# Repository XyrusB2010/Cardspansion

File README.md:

# Cardspansion
A modular microcontroller system, featuring a customizable MCU

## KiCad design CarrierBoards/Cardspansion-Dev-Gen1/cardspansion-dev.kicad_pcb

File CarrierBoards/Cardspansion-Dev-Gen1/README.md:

# Cardspansion-Dev
This is the first carrier board for the Cardspansion series. It breaks out all of the supported interfaces of the cardspansion-gen1 series (including SDIO, I2S, JTAG, SPI, SWDIO, I2C, and UART). The board also features a CR2032 battery holder for RTC. A DC barrel jack is included, and can handle a voltage up to 12V. Unlike Arduino UNOs, there is a manual switch for selecting the voltage source between USB and DC. The board has 6 LEDs, which indicate power, user LEDs, and UART signals. Most of the components are SMD, except for the DC barrel jack. At the top centre, two push buttons are included for BOOT and RESET, which most MCUs use. PLEASE DO NOT power the board via the 5V pins, as they will damage the onboard voltage regulators. This dev board may be forwards compatible with following generations, although features exclusive to other generations will not be fully compatible. 
## Features
- Supports cardspansion-gen1 cards
- All cardspansion-gen1 interfaces broken out
- Onboard CR2032 battery holder for RTC
- External DC source supported (6-12V)
- Physical slide switch for 5V voltage source (DC Jack, USB)
- LEDs for 3.3V, 5V, 2 User LEDs, UART
- Push buttons for RESET and BOOT
## PCB Render

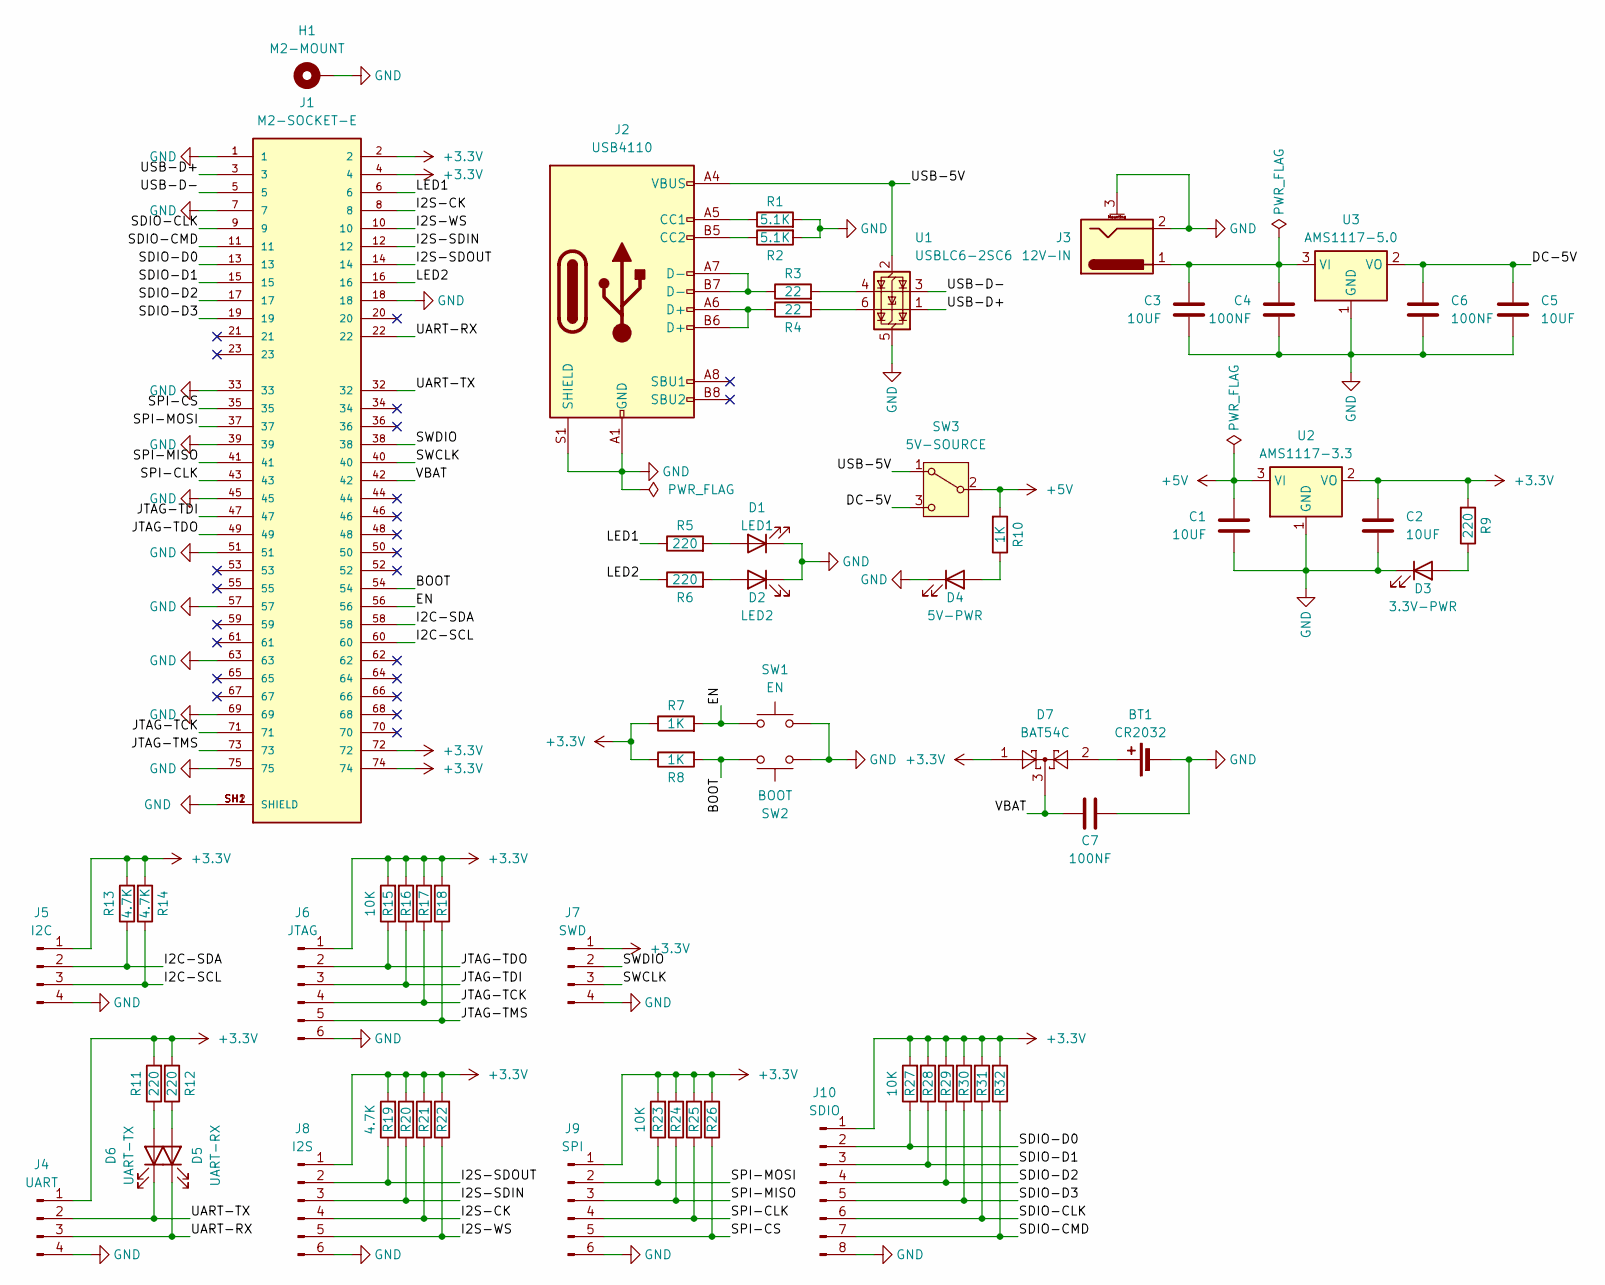
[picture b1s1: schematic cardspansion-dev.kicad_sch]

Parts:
BT1: CR2032; BatteryHolder_Multicomp_BC-2001_1x2032
C1, C2, C3, C5: 10UF; C_0805_2012Metric
C4, C6, C7: 100NF; C_0805_2012Metric
D1: LED1; LED_0805_2012Metric
D2: LED2; LED_0805_2012Metric
D3: 3.3V-PWR; LED_0805_2012Metric
D4: 5V-PWR; LED_0805_2012Metric
D5: UART-RX; LED_0805_2012Metric
D6: UART-TX; LED_0805_2012Metric
D7: BAT54C; SOT-23
H1: M2-MOUNT; MountingHole_2.2mm_M2_Pad
J1: M2-SOCKET-E; TE_2199119-4; PARTREV D
J2: USB4110; USB_C_Receptacle_GCT_USB4110
J3: 12V-IN; BarrelJack_Horizontal
J4: UART; PinHeader_1x04_P2.54mm_Vertical_SMD_Pin1Left
J5: I2C; PinHeader_1x04_P2.54mm_Vertical_SMD_Pin1Left
J6: JTAG; PinHeader_1x06_P2.54mm_Vertical_SMD_Pin1Left
J7: SWD; PinHeader_1x04_P2.54mm_Vertical_SMD_Pin1Left
J8: I2S; PinHeader_1x06_P2.54mm_Vertical_SMD_Pin1Left
J9: SPI; PinHeader_1x06_P2.54mm_Vertical_SMD_Pin1Left
J10: SDIO; PinHeader_1x08_P2.54mm_Vertical_SMD_Pin1Left
R1, R2: 5.1K; R_0805_2012Metric
R3, R4: 22; R_0805_2012Metric
R5, R6, R9, R11, R12: 220; R_0805_2012Metric
R7, R8, R10: 1K; R_0805_2012Metric
R13, R14, R19, R20, R21, R22: 4.7K; R_0805_2012Metric
R15, R16, R17, R18, R23, R24, R25, R26, R27, R28, R29, R30, R31, R32: 10K; R_0805_2012Metric
SW1: EN; SW_Tactile_SPST_NO_Straight_CK_PTS636Sx25SMTRLFS
SW2: BOOT; SW_Tactile_SPST_NO_Straight_CK_PTS636Sx25SMTRLFS
SW3: 5V-SOURCE; SW_SPDT_CK_JS102011SAQN
U1: USBLC6-2SC6; SOT-23-6
U2: AMS1117-3.3; SOT-223-3_TabPin2
U3: AMS1117-5.0; SOT-223-3_TabPin2

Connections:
+3.3V: C2.1, D7.1, J1.2, J1.4, J1.72, J1.74, J4.1, J5.1, J6.1, J7.1, J8.1, J9.1, J10.1, R7.1, R8.1, R9.2, R11.2, R12.2, R13.2, R14.2, R15.2, R16.2, R17.2, R18.2, R19.2, R20.2, R21.2, R22.2, R23.2, R24.2, R25.2, R26.2, R27.2, R28.2, R29.2, R30.2, R31.2, R32.2, U2.2 (VO)
+5V: C1.1, R10.2, SW3.2 (B), U2.3 (VI)
/BOOT: J1.54, R8.2, SW2.1
/DC-5V: C5.1, C6.1, SW3.3 (C), U3.2 (VO)
/EN: J1.56, R7.2, SW1.1
/I2C-SCL: J1.60, J5.3, R14.1
/I2C-SDA: J1.58, J5.2, R13.1
/I2S-CK: J1.8, J8.4, R21.1
/I2S-SDIN: J1.12, J8.3, R20.1
/I2S-SDOUT: J1.14, J8.2, R19.1
/I2S-WS: J1.10, J8.5, R22.1
/JTAG-TCK: J1.71, J6.4, R17.1
/JTAG-TDI: J1.47, J6.3, R16.1
/JTAG-TDO: J1.49, J6.2, R15.1
/JTAG-TMS: J1.73, J6.5, R18.1
/LED1: J1.6, R5.1
/LED2: J1.16, R6.1
/SDIO-CLK: J1.9, J10.6, R31.1
/SDIO-CMD: J1.11, J10.7, R32.1
/SDIO-D0: J1.13, J10.2, R27.1
/SDIO-D1: J1.15, J10.3, R28.1
/SDIO-D2: J1.17, J10.4, R29.1
/SDIO-D3: J1.19, J10.5, R30.1
/SPI-CLK: J1.43, J9.4, R25.1
/SPI-CS: J1.35, J9.5, R26.1
/SPI-MISO: J1.41, J9.3, R24.1
/SPI-MOSI: J1.37, J9.2, R23.1
/SWCLK: J1.40, J7.3
/SWDIO: J1.38, J7.2
/UART-RX: D5.1 (K), J1.22, J4.3
/UART-TX: D6.1 (K), J1.32, J4.2
/USB-5V: J2.A4 (VBUS), J2.A9 (VBUS), J2.B4 (VBUS), J2.B9 (VBUS), SW3.1 (A), U1.2 (GND)
/USB-D+: J1.3, U1.1 (I/O1)
/USB-D-: J1.5, U1.3 (I/O2)
/VBAT: C7.1, D7.3, J1.42
GND: BT1.2 (-), C1.2, C2.2, C3.2, C4.2, C5.2, C6.2, C7.2, D1.1 (K), D2.1 (K), D3.1 (K), D4.1 (K), H1.1 (MP), J1.1, J1.7, J1.18, J1.33, J1.39, J1.45, J1.51, J1.57, J1.63, J1.69, J1.75, J1.SH1 (SHIELD), J1.SH2 (SHIELD), J2.A1 (GND), J2.A12 (GND), J2.B1 (GND), J2.B12 (GND), J2.S1 (SHIELD), J3.2, J3.3 (MountPin), J4.4, J5.4, J6.6, J7.4, J8.6, J9.6, J10.8, R1.2, R2.2, SW1.2, SW2.2, U1.5 (VBUS), U2.1 (GND), U3.1 (GND)
unnamed: BT1.1 (+), D7.2
unnamed: D1.2 (A), R5.2
unnamed: D2.2 (A), R6.2
unnamed: D3.2 (A), R9.1
unnamed: D4.2 (A), R10.1
unnamed: D5.2 (A), R12.1
unnamed: D6.2 (A), R11.1
unnamed: J2.A5 (CC1), R1.1
unnamed: J2.B5 (CC2), R2.1
unnamed: J2.A6 (D+), J2.B6 (D+), R4.1
unnamed: J2.A7 (D-), J2.B7 (D-), R3.1
unnamed: R3.2, U1.4 (I/O2)
unnamed: R4.2, U1.6 (I/O1)
unnamed: C3.1, C4.1, J3.1, U3.3 (VI)

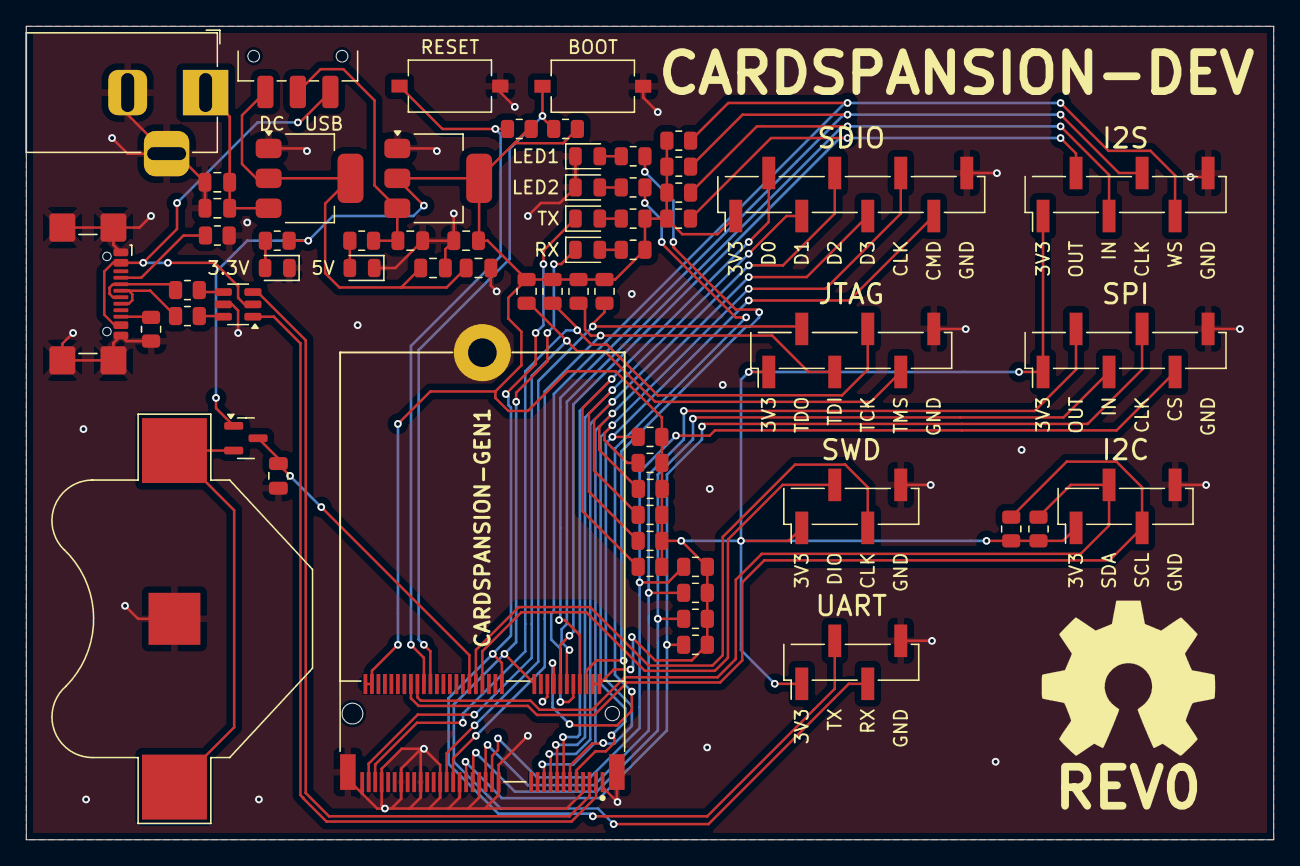
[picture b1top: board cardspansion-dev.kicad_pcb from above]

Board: 2 copper layers, 96.0 x 62.6 mm, 64 parts (0 on the bottom side), 50 nets.

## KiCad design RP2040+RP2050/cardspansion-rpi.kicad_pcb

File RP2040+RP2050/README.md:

# Cardspansion-RPI
The Cardspansion-RPI is the 4th and final MCU to be added to the first generation of the Cardspansion series. It is reccomended to use the Waveshare RP2350-Tiny board, but the RP2040-Tiny is also compatible, at the cost of losing UART, I2C, and LEDs (Will be fixed in a later revision). If you do use the RP2350-Tiny, you also gain access to the SPI, I2S and USB interfaces. The RP2350 and RP2040 have a dedicated USB header on board, but you will need an FPC breakout in order to use it. Just like the Cardspansion-NRF, the Raspberry Pi board is very large, so the silkscreen text on the front layer has to be placed on the side.
## Features
- I2C (RP2350 only)
- UART (RP2350 only)
- SPI
- USB-OTG functionality (Host on dedicated USB pin, OTG configured on PIO)
- 2 LEDs (broken out for carrier board)
## PCB Render

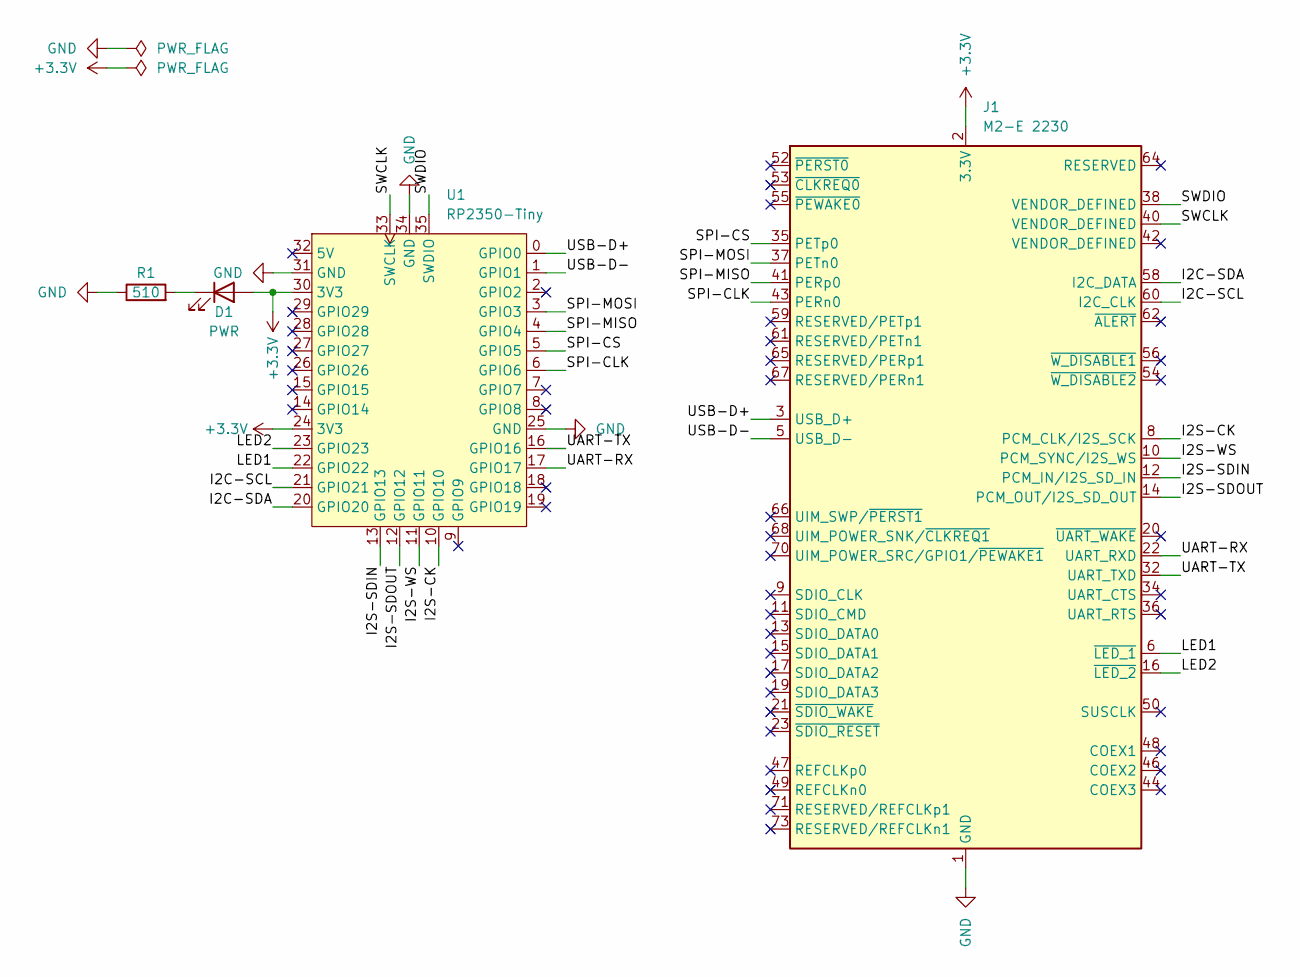
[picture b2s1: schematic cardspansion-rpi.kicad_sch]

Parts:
D1: PWR; LED_0805_2012Metric
J1: M2-E 2230; M2-2230-E
R1: 510; R_0805_2012Metric
U1: RP2350-Tiny

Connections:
+3.3V: D1.2 (A), J1.2 (3.3V), J1.4 (3.3V), J1.72 (3.3V), J1.74 (3.3V), U1.24 (3V3), U1.30 (3V3)
/I2C-SCL: J1.60 (I2C_CLK), U1.21 (GPIO21)
/I2C-SDA: J1.58 (I2C_DATA), U1.20 (GPIO20)
/I2S-CK: J1.8 (PCM_CLK/I2S_SCK), U1.10 (GPIO10)
/I2S-SDIN: J1.12 (PCM_IN/I2S_SD_IN), U1.13 (GPIO13)
/I2S-SDOUT: J1.14 (PCM_OUT/I2S_SD_OUT), U1.12 (GPIO12)
/I2S-WS: J1.10 (PCM_SYNC/I2S_WS), U1.11 (GPIO11)
/LED1: J1.6 (~LED_1), U1.22 (GPIO22)
/LED2: J1.16 (~LED_2), U1.23 (GPIO23)
/SPI-CLK: J1.43 (PERn0), U1.6 (GPIO6)
/SPI-CS: J1.35 (PETp0), U1.5 (GPIO5)
/SPI-MISO: J1.41 (PERp0), U1.4 (GPIO4)
/SPI-MOSI: J1.37 (PETn0), U1.3 (GPIO3)
/SWCLK: J1.40 (VENDOR_DEFINED), U1.33 (SWCLK)
/SWDIO: J1.38 (VENDOR_DEFINED), U1.35 (SWDIO)
/UART-RX: J1.22 (UART_RXD), U1.17 (GPIO17)
/UART-TX: J1.32 (UART_TXD), U1.16 (GPIO16)
/USB-D+: J1.3 (USB_D+), U1.0 (GPIO0)
/USB-D-: J1.5 (USB_D-), U1.1 (GPIO1)
GND: J1.1 (GND), J1.7 (GND), J1.18 (GND), J1.33 (GND), J1.39 (GND), J1.45 (GND), J1.51 (GND), J1.57 (GND), J1.63 (GND), J1.69 (GND), J1.75 (GND), R1.1, U1.25 (GND), U1.31 (GND), U1.34 (GND)
unnamed: D1.1 (K), R1.2

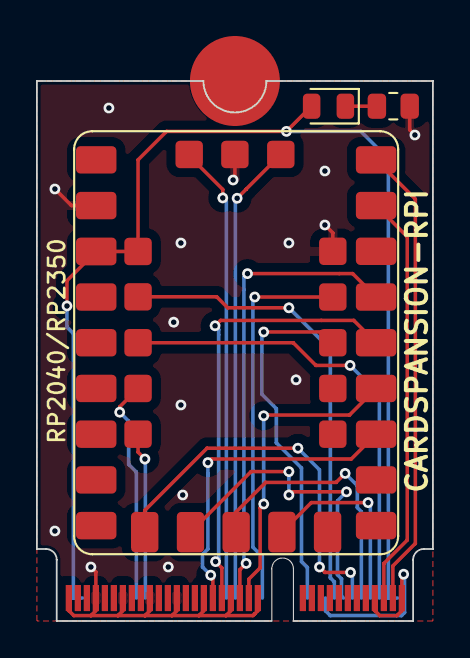
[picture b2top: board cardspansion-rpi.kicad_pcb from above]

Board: 2 copper layers, 22.0 x 30.0 mm, 4 parts (0 on the bottom side), 21 nets.

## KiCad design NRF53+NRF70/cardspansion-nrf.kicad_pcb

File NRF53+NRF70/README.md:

# Cardspansion-NRF
The third MCU to be added to the Cardspansion series, it features the Minewsemi ME16WS03. It is a Wi-Fi 6 + BLE combo module, which contains both an NRF5340 and NRF7002. The module contains two U.FL connectors, and there is a keepout zone to avoid external noise from reaching the components. There are no need for external crystals, as they are already included inside the module. Compared to the previous Cardspansion modules however, this module is larger in size, so the text has to be relocated to the side of the card.
## Features
- I2C
- UART
- SPI
- RTC support
- SWDIO
- I2S (Input and Output)
- 2 LEDs (broken out for carrier board)
## PCB Render

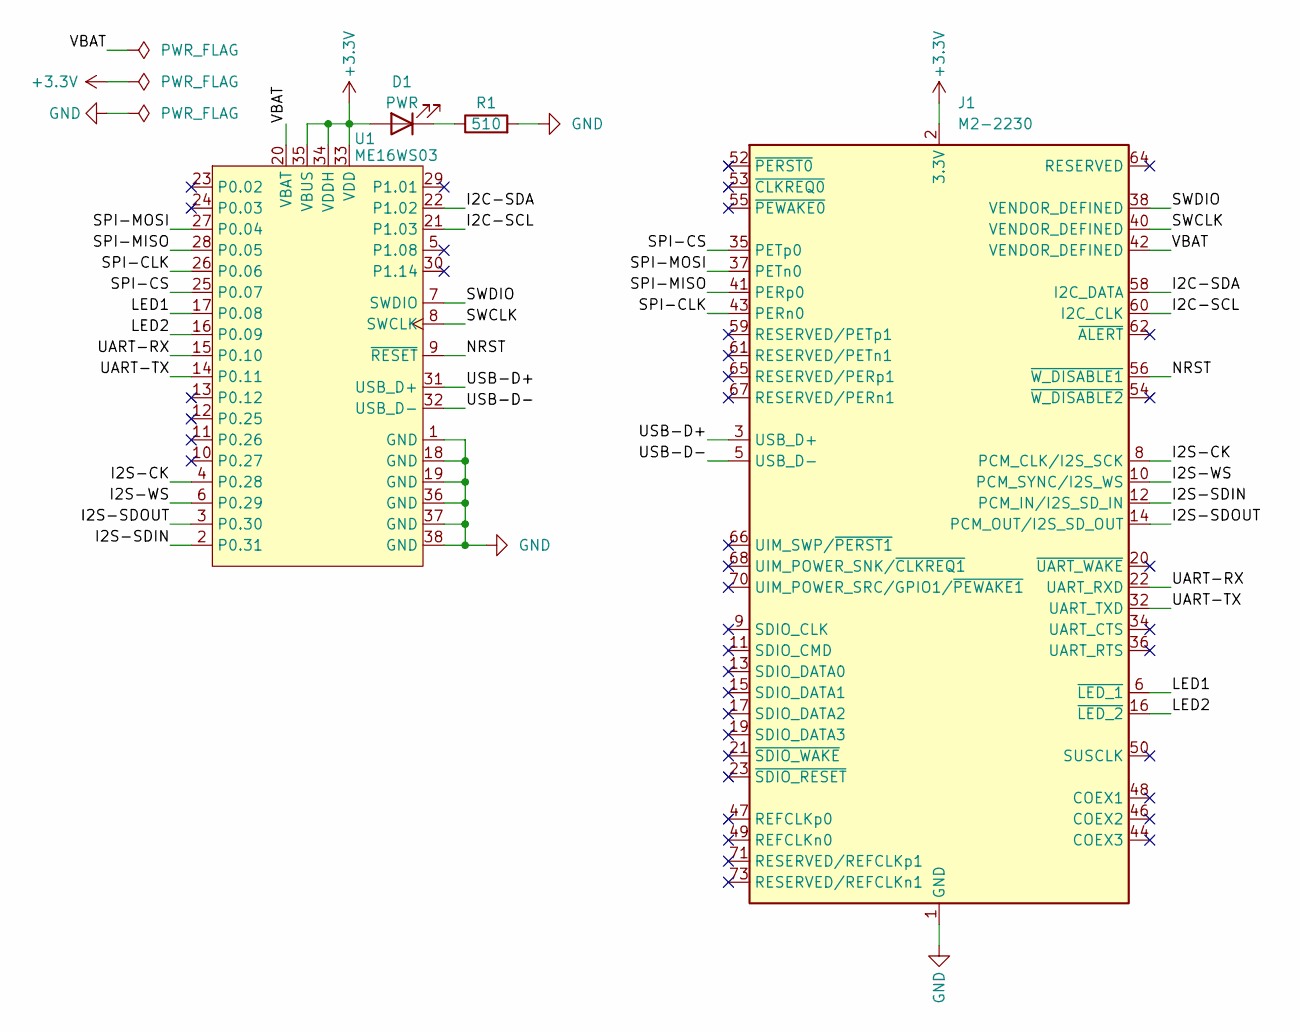
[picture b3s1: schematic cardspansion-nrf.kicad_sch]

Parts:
D1: PWR; LED_0805_2012Metric
J1: M2-2230; M2-2230-E
R1: 510; R_0805_2012Metric
U1: ME16WS03

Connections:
+3.3V: D1.2 (A), J1.2 (3.3V), J1.4 (3.3V), J1.72 (3.3V), J1.74 (3.3V), U1.33 (VDD), U1.34 (VDDH), U1.35 (VBUS)
/I2C-SCL: J1.60 (I2C_CLK), U1.21 (P1.03)
/I2C-SDA: J1.58 (I2C_DATA), U1.22 (P1.02)
/I2S-CK: J1.8 (PCM_CLK/I2S_SCK), U1.4 (P0.28)
/I2S-SDIN: J1.12 (PCM_IN/I2S_SD_IN), U1.2 (P0.31)
/I2S-SDOUT: J1.14 (PCM_OUT/I2S_SD_OUT), U1.3 (P0.30)
/I2S-WS: J1.10 (PCM_SYNC/I2S_WS), U1.6 (P0.29)
/LED1: J1.6 (~LED_1), U1.17 (P0.08)
/LED2: J1.16 (~LED_2), U1.16 (P0.09)
/NRST: J1.56 (~W_DISABLE1), U1.9 (~RESET)
/SPI-CLK: J1.43 (PERn0), U1.26 (P0.06)
/SPI-CS: J1.35 (PETp0), U1.25 (P0.07)
/SPI-MISO: J1.41 (PERp0), U1.28 (P0.05)
/SPI-MOSI: J1.37 (PETn0), U1.27 (P0.04)
/SWCLK: J1.40 (VENDOR_DEFINED), U1.8 (SWCLK)
/SWDIO: J1.38 (VENDOR_DEFINED), U1.7 (SWDIO)
/UART-RX: J1.22 (UART_RXD), U1.15 (P0.10)
/UART-TX: J1.32 (UART_TXD), U1.14 (P0.11)
/USB-D+: J1.3 (USB_D+), U1.31 (USB_D+)
/USB-D-: J1.5 (USB_D-), U1.32 (USB_D-)
/VBAT: J1.42 (VENDOR_DEFINED), U1.20 (VBAT)
GND: J1.1 (GND), J1.7 (GND), J1.18 (GND), J1.33 (GND), J1.39 (GND), J1.45 (GND), J1.51 (GND), J1.57 (GND), J1.63 (GND), J1.69 (GND), J1.75 (GND), R1.2, U1.1 (GND), U1.18 (GND), U1.19 (GND), U1.36 (GND), U1.37 (GND), U1.38 (GND)
unnamed: D1.1 (K), R1.1

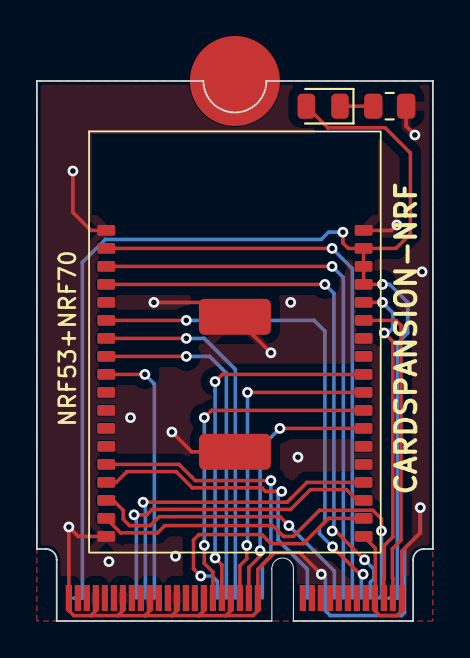
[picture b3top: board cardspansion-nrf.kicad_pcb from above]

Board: 2 copper layers, 22.0 x 30.0 mm, 4 parts (0 on the bottom side), 23 nets.

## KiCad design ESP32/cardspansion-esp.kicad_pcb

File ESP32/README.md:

# Cardspansion-ESP
This is the second MCU to be implemented into the Cardspansion series. Featuring an ESP32-WROOM-32UE, it is suited for applications requiring wireless connectivity (Wi-Fi and/or BLE). Because the ESP32 has no need for an 8MHz crystal, this card should have a simpler design. Unlike the STM32U5, it also comes with a different set of features (JTAG & SPI). Please note that this board does not directly interface USB due to the lack of a controller in the MCU.
## Features
- I2C
- UART
- SPI
- JTAG
- I2S (including support for input)
- 2 LEDs (broken out for carrier board)
## PCB Render

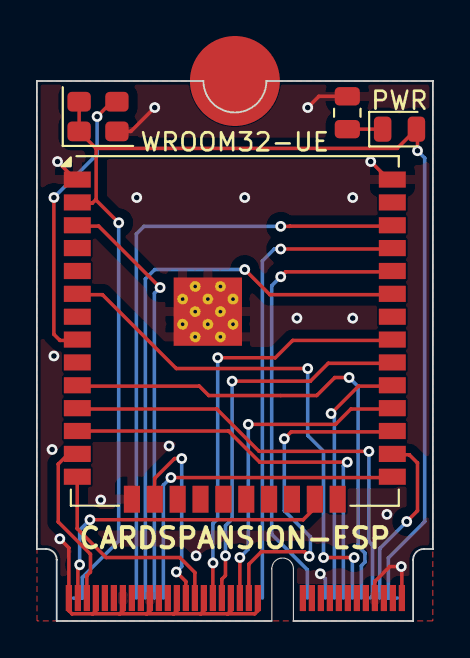
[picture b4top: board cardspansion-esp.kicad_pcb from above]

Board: 2 copper layers, 22.0 x 30.0 mm, 5 parts (0 on the bottom side), 24 nets.

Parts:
D1: PWR; LED_0805_2012Metric
J1: M2-E 2230; M2-2230-E
R1: 510; R_0805_2012Metric
WROOM32-UE: CARDSPANSION-ESP; ESP32-WROOM-32UE
Y1: ASE-32.768KHZ; Oscillator_SMD_Abracon_ASE-4Pin_3.2x2.5mm

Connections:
+3.3V: D1.2 (A), J1.2 (3.3V), J1.4 (3.3V), J1.72 (3.3V), J1.74 (3.3V), WROOM32-UE.2 (VDD), Y1.1 (EN), Y1.4 (Vdd)
/BOOT: J1.54 (~W_DISABLE2), WROOM32-UE.25 (IO0)
/EN: J1.56 (~W_DISABLE1), WROOM32-UE.3 (EN)
/I2C-SCL: J1.60 (I2C_CLK), WROOM32-UE.36 (IO22)
/I2C-SDA: J1.58 (I2C_DATA), WROOM32-UE.33 (IO21)
/I2S-CK: J1.8 (PCM_CLK/I2S_SCK), WROOM32-UE.11 (IO26)
/I2S-SDIN: J1.12 (PCM_IN/I2S_SD_IN), WROOM32-UE.6 (IO34)
/I2S-SDOUT: J1.14 (PCM_OUT/I2S_SD_OUT), WROOM32-UE.12 (IO27)
/I2S-WS: J1.10 (PCM_SYNC/I2S_WS), WROOM32-UE.10 (IO25)
/JTAG-TCK: J1.71 (RESERVED/REFCLKp1), WROOM32-UE.13 (IO14)
/JTAG-TDI: J1.47 (REFCLKp0), WROOM32-UE.14 (IO12)
/JTAG-TDO: J1.49 (REFCLKn0), WROOM32-UE.16 (IO13)
/JTAG-TMS: J1.73 (RESERVED/REFCLKn1), WROOM32-UE.23 (IO15)
/LED1: J1.6 (~LED_1), WROOM32-UE.26 (IO4)
/LED2: J1.16 (~LED_2), WROOM32-UE.29 (IO5)
/RTCIN: WROOM32-UE.8 (IO32), Y1.3 (OUT)
/SPI-CLK: J1.43 (PERn0), WROOM32-UE.31 (IO19)
/SPI-CS: J1.35 (PETp0), WROOM32-UE.27 (IO16)
/SPI-MISO: J1.41 (PERp0), WROOM32-UE.30 (IO18)
/SPI-MOSI: J1.37 (PETn0), WROOM32-UE.28 (IO17)
/UART-RX: J1.22 (UART_RXD), WROOM32-UE.34 (RXD0/IO3)
/UART-TX: J1.32 (UART_TXD), WROOM32-UE.35 (TXD0/IO1)
GND: J1.1 (GND), J1.7 (GND), J1.18 (GND), J1.33 (GND), J1.39 (GND), J1.45 (GND), J1.51 (GND), J1.57 (GND), J1.63 (GND), J1.69 (GND), J1.75 (GND), R1.2, WROOM32-UE.1 (GND), WROOM32-UE.15 (GND), WROOM32-UE.38 (GND), WROOM32-UE.39 (GND), Y1.2 (GND)
unnamed: D1.1 (K), R1.1

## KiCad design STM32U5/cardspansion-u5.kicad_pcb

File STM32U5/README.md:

# Cardspansion-U5
The first MCU of the series, the Cardspansion-U5 features a STM32U575CITX. It is best suited for low power applications which may still require lots of processing performance. This card features also features two crystal oscillators (ASE 8MHz and ASEK 32.768KHz) to drive the STM32U5's low power and RTC clock.
## Features
- STM32U575CITX
- I2C
- UART
- SDIO
- USB
- SWD
- I2S
- 2 LEDs (broken out for carrier board)
## PCB Render

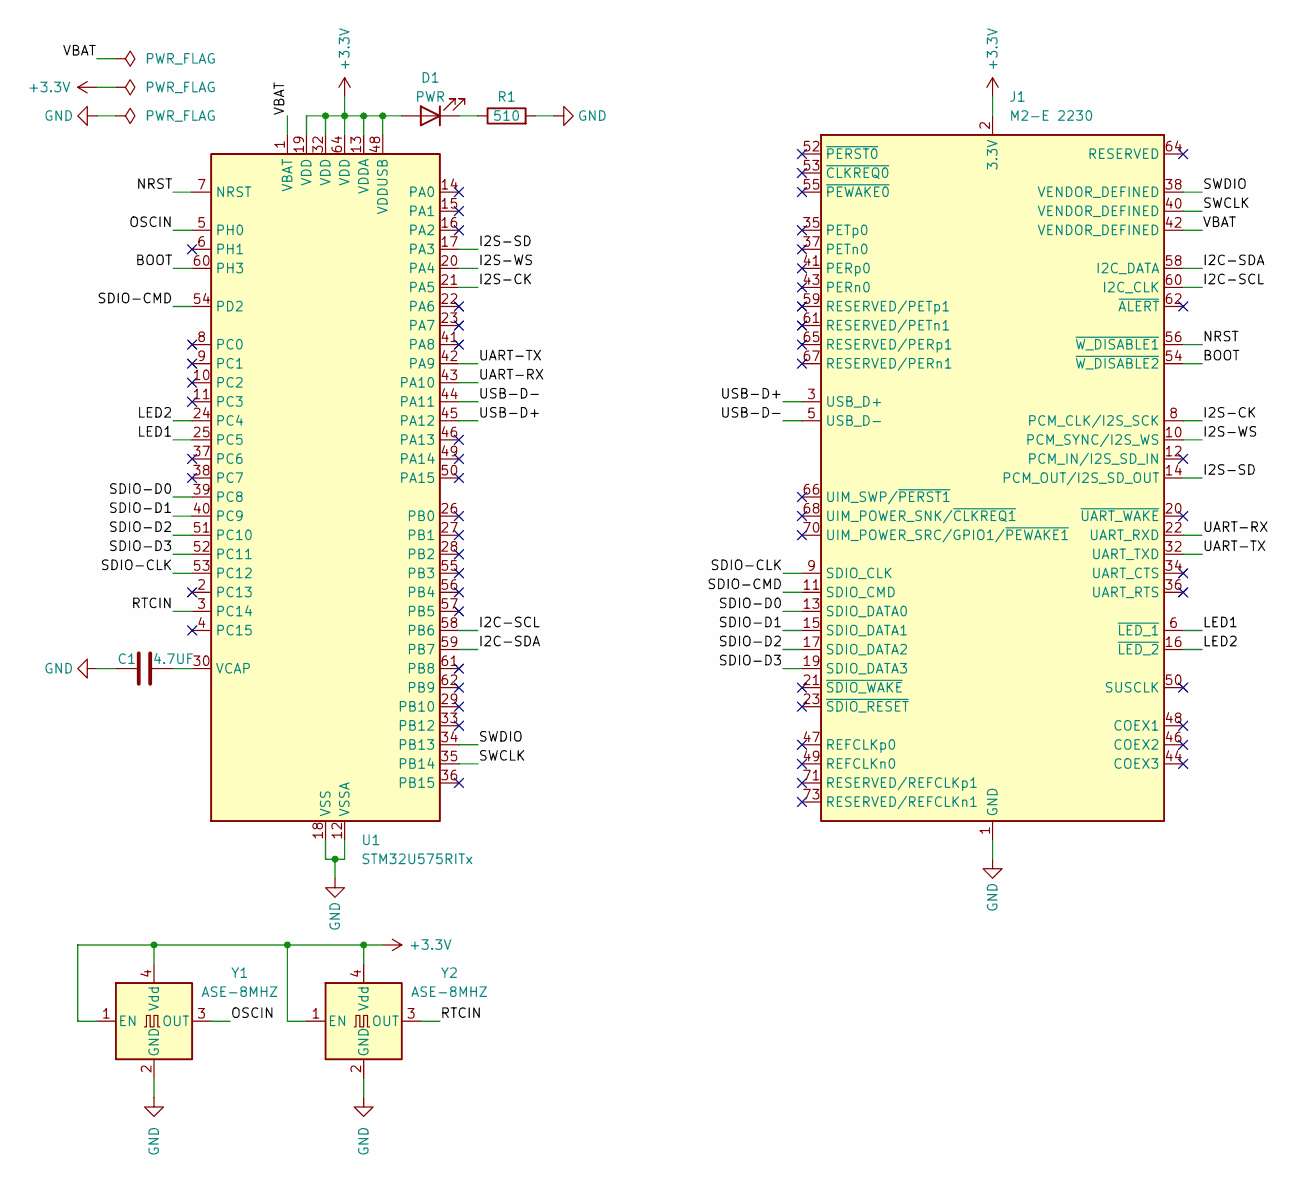
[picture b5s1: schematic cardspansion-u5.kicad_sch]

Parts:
C1: 4.7UF; C_0805_2012Metric
D1: PWR; LED_0805_2012Metric
J1: M2-E 2230; M2-2230-E
R1: 510; R_0805_2012Metric
U1: STM32U575RITx; LQFP-64_10x10mm_P0.5mm
Y1, Y2: ASE-8MHZ; Oscillator_SMD_Abracon_ASE-4Pin_3.2x2.5mm

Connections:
+3.3V: D1.2 (A), J1.2 (3.3V), J1.4 (3.3V), J1.72 (3.3V), J1.74 (3.3V), U1.13 (VDDA), U1.19 (VDD), U1.32 (VDD), U1.48 (VDDUSB), U1.64 (VDD), Y1.1 (EN), Y1.4 (Vdd), Y2.1 (EN), Y2.4 (Vdd)
/BOOT: J1.54 (~W_DISABLE2), U1.60 (PH3)
/I2C-SCL: J1.60 (I2C_CLK), U1.58 (PB6)
/I2C-SDA: J1.58 (I2C_DATA), U1.59 (PB7)
/I2S-CK: J1.8 (PCM_CLK/I2S_SCK), U1.21 (PA5)
/I2S-SD: J1.14 (PCM_OUT/I2S_SD_OUT), U1.17 (PA3)
/I2S-WS: J1.10 (PCM_SYNC/I2S_WS), U1.20 (PA4)
/LED1: J1.6 (~LED_1), U1.25 (PC5)
/LED2: J1.16 (~LED_2), U1.24 (PC4)
/NRST: J1.56 (~W_DISABLE1), U1.7 (NRST)
/OSCIN: U1.5 (PH0), Y1.3 (OUT)
/RTCIN: U1.3 (PC14), Y2.3 (OUT)
/SDIO-CLK: J1.9 (SDIO_CLK), U1.53 (PC12)
/SDIO-CMD: J1.11 (SDIO_CMD), U1.54 (PD2)
/SDIO-D0: J1.13 (SDIO_DATA0), U1.39 (PC8)
/SDIO-D1: J1.15 (SDIO_DATA1), U1.40 (PC9)
/SDIO-D2: J1.17 (SDIO_DATA2), U1.51 (PC10)
/SDIO-D3: J1.19 (SDIO_DATA3), U1.52 (PC11)
/SWCLK: J1.40 (VENDOR_DEFINED), U1.35 (PB14)
/SWDIO: J1.38 (VENDOR_DEFINED), U1.34 (PB13)
/UART-RX: J1.22 (UART_RXD), U1.43 (PA10)
/UART-TX: J1.32 (UART_TXD), U1.42 (PA9)
/USB-D+: J1.3 (USB_D+), U1.45 (PA12)
/USB-D-: J1.5 (USB_D-), U1.44 (PA11)
/VBAT: J1.42 (VENDOR_DEFINED), U1.1 (VBAT)
GND: C1.1, J1.1 (GND), J1.7 (GND), J1.18 (GND), J1.33 (GND), J1.39 (GND), J1.45 (GND), J1.51 (GND), J1.57 (GND), J1.63 (GND), J1.69 (GND), J1.75 (GND), R1.2, U1.12 (VSSA), U1.18 (VSS), U1.31 (VSS), U1.47 (VSS), U1.63 (VSS), Y1.2 (GND), Y2.2 (GND)
unnamed: D1.1 (K), R1.1
unnamed: C1.2, U1.30 (VCAP)

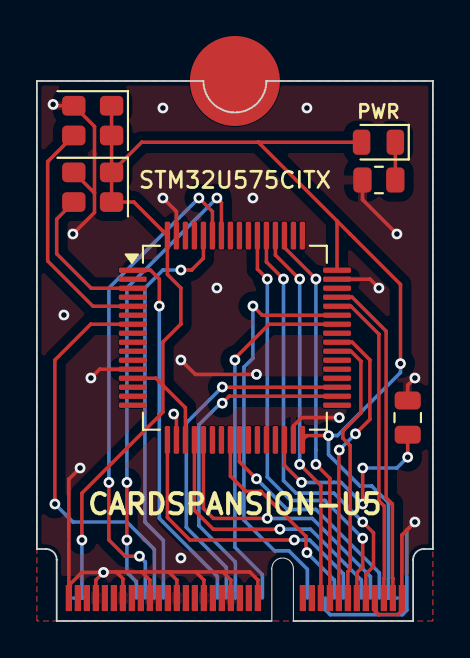
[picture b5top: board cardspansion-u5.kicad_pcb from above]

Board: 2 copper layers, 22.0 x 30.0 mm, 7 parts (0 on the bottom side), 28 nets.

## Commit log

2025-08-13 Add cardspansion-u5.zip
2025-08-15 Upload cardspansion-esp files
2025-08-15 Rename cardspansion-esp.md to README.md
2025-08-15 Rename cardspansion-u5.md to README.md
2025-08-15 Upload cardspansion-u5 files
2025-08-27 Create README.md
    Cardspansion-NRF
2025-08-27 Update README.md
    Add cardspansion-esp PCB renders
2025-08-27 Upload cardspansion-nrf files
2025-08-29 Add README for Cardspansion-RPI
    Added detailed information about the Cardspansion-RPI MCU, including features and PCB render images.
2025-08-29 Upload cardspansion-rpi files
2025-08-29 Add MIT License
2025-09-02 Fix cardspansion-esp I2S wiring
    I2S-SDIN and I2S-SDOUT nets were switched around
2025-09-02 Fix cardspansion-nrf I2S wiring
    I2S-SDIN and I2S-SDOUT nets were switched around
2025-09-02 Fix cardspansion-rpi I2S wiring
    I2S-SDIN and I2S-SDOUT nets were switched around
2025-09-18 Create README.md
    Cardspansion-Dev-Gen1
2025-09-18 Upload cardspansion-dev files
